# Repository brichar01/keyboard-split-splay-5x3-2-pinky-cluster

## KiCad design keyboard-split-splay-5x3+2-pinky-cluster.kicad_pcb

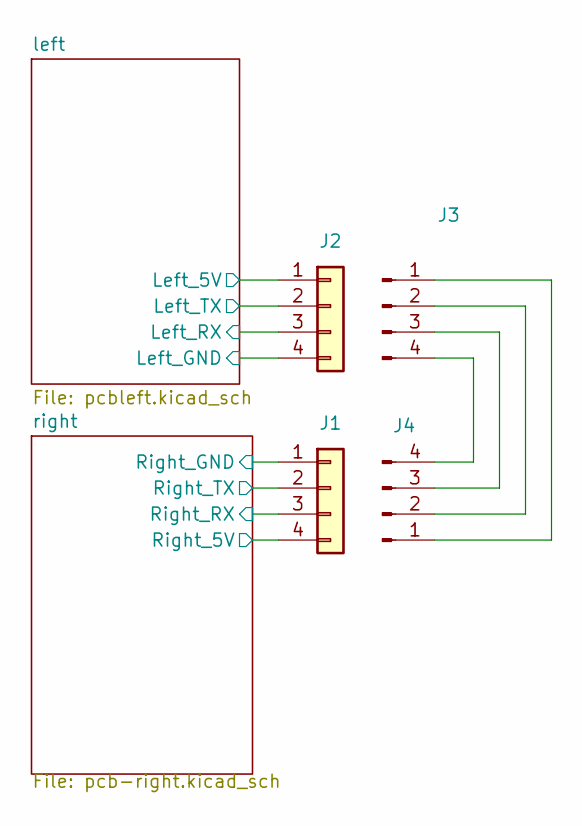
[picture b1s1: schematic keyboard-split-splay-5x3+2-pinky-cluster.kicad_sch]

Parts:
J1, J2: JST_SM04B-SR_R
J3, J4: Conn_01x04_Pin

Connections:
/left/LRX: J2.3; also elsewhere on the board
/left/LTX: J2.2; also elsewhere on the board
/left/L_5V: J2.1; also elsewhere on the board
/left/L_GND: J2.4; also elsewhere on the board
/right/RRX: J1.3; also elsewhere on the board
/right/RTX: J1.2; also elsewhere on the board
/right/R_5V: J1.4; also elsewhere on the board
/right/R_GND: J1.1; also elsewhere on the board
unnamed: J3.1, J4.1
unnamed: J3.2, J4.2
unnamed: J3.3, J4.3
unnamed: J3.4, J4.4

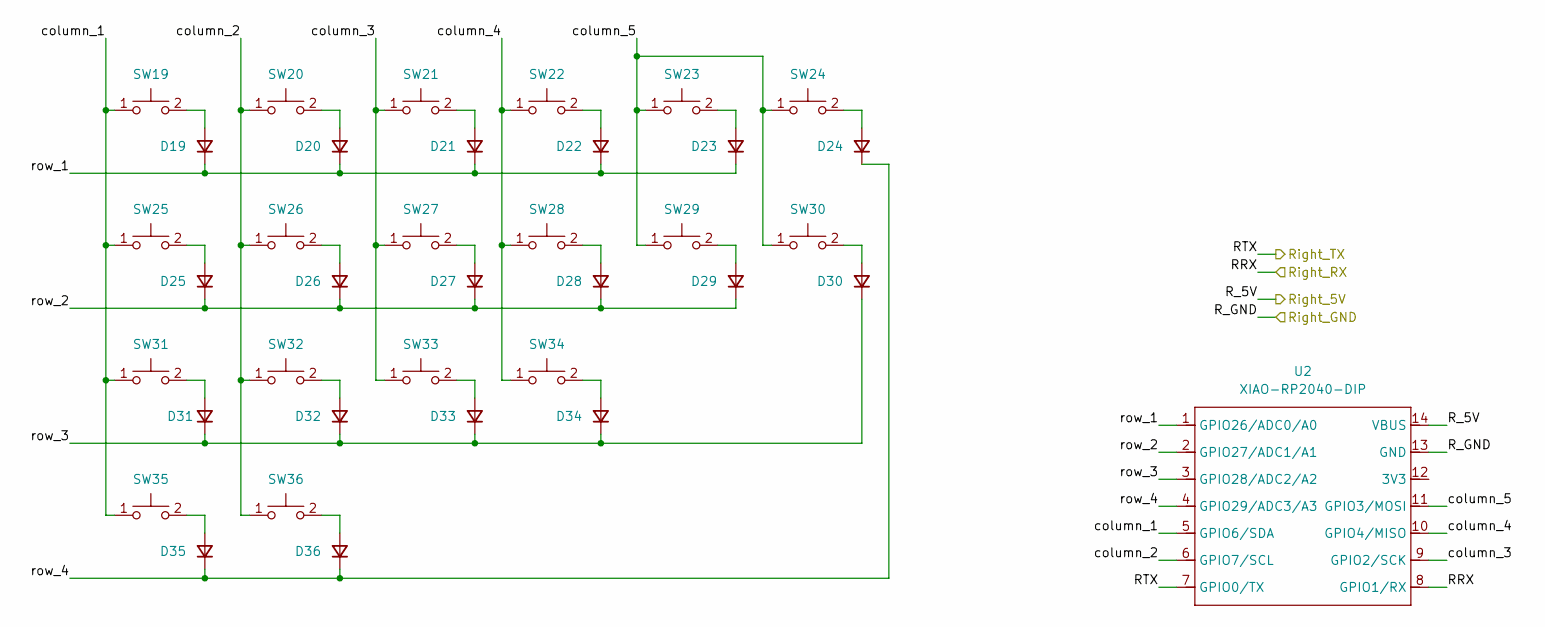
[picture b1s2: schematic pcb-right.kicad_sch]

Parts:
D19, D20, D21, D22, D23, D24, D25, D26, D27, D28, D29, D30, D31, D32, D33, D34, D35, D36: Val; GENERIC_DO-35_A
SW19, SW20, SW21, SW22, SW23, SW24, SW25, SW26, SW27, SW28, SW29, SW30, SW31, SW32, SW33, SW34, SW35, SW36: GENERIC_ELECTROMECHANICAL_PUSHBUTTON; GATEREON_KS-2P02B01-01-a_R
U2: XIAO-RP2040-DIP; SEEED_XIAO-RP2040_T-DIP

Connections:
/right/RRX: U2.8 (GPIO1/RX); also elsewhere on the board
/right/RTX: U2.7 (GPIO0/TX); also elsewhere on the board
/right/R_5V: U2.14 (VBUS); also elsewhere on the board
/right/R_GND: U2.13 (GND); also elsewhere on the board
/right/column_1: SW19.1 (2), SW25.1 (2), SW31.1 (2), SW35.1 (2), U2.5 (GPIO6/SDA)
/right/column_2: SW20.1 (2), SW26.1 (2), SW32.1 (2), SW36.1 (2), U2.6 (GPIO7/SCL)
/right/column_3: SW21.1 (2), SW27.1 (2), SW33.1 (2), U2.9 (GPIO2/SCK)
/right/column_4: SW22.1 (2), SW28.1 (2), SW34.1 (2), U2.10 (GPIO4/MISO)
/right/column_5: SW23.1 (2), SW24.1 (2), SW29.1 (2), SW30.1 (2), U2.11 (GPIO3/MOSI)
/right/row_1: D19.1 (K), D20.1 (K), D21.1 (K), D22.1 (K), D23.1 (K), U2.1 (GPIO26/ADC0/A0)
/right/row_2: D25.1 (K), D26.1 (K), D27.1 (K), D28.1 (K), D29.1 (K), U2.2 (GPIO27/ADC1/A1)
/right/row_3: D30.1 (K), D31.1 (K), D32.1 (K), D33.1 (K), D34.1 (K), U2.3 (GPIO28/ADC2/A2)
/right/row_4: D24.1 (K), D35.1 (K), D36.1 (K), U2.4 (GPIO29/ADC3/A3)
unnamed: D19.2 (A), SW19.2
unnamed: D20.2 (A), SW20.2
unnamed: D21.2 (A), SW21.2
unnamed: D22.2 (A), SW22.2
unnamed: D23.2 (A), SW23.2
unnamed: D24.2 (A), SW24.2
unnamed: D25.2 (A), SW25.2
unnamed: D26.2 (A), SW26.2
unnamed: D27.2 (A), SW27.2
unnamed: D28.2 (A), SW28.2
unnamed: D29.2 (A), SW29.2
unnamed: D30.2 (A), SW30.2
unnamed: D31.2 (A), SW31.2
unnamed: D32.2 (A), SW32.2
unnamed: D33.2 (A), SW33.2
unnamed: D34.2 (A), SW34.2
unnamed: D35.2 (A), SW35.2
unnamed: D36.2 (A), SW36.2

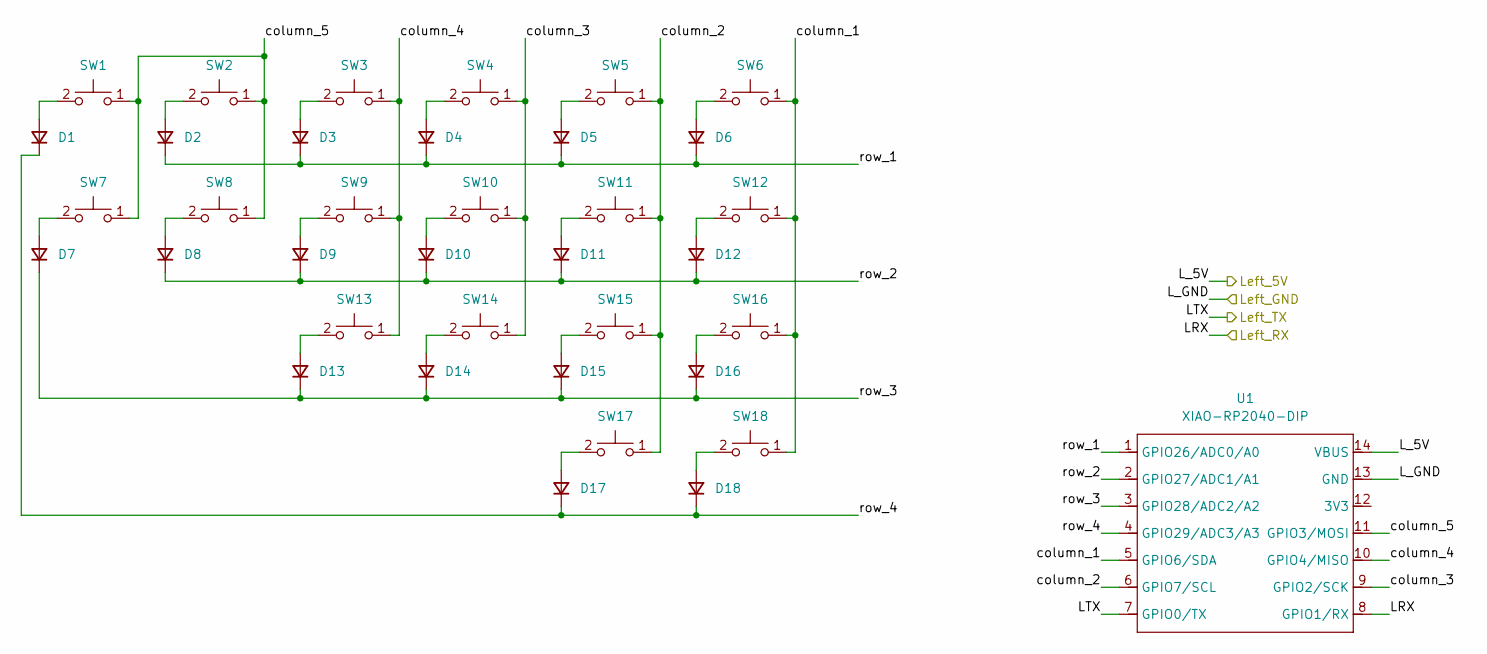
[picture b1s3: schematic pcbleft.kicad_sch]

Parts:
D1, D2, D3, D4, D5, D6, D7, D8, D9, D10, D11, D12, D13, D14, D15, D16, D17, D18: Val; GENERIC_DO-35_A
SW1, SW2, SW3, SW4, SW5, SW6, SW7, SW8, SW9, SW10, SW11, SW12, SW13, SW14, SW15, SW16, SW17, SW18: GENERIC_ELECTROMECHANICAL_PUSHBUTTON; GATEREON_KS-2P02B01-01-a_R
U1: XIAO-RP2040-DIP; SEEED_XIAO-RP2040_T-DIP

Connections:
/left/LRX: U1.8 (GPIO1/RX); also elsewhere on the board
/left/LTX: U1.7 (GPIO0/TX); also elsewhere on the board
/left/L_5V: U1.14 (VBUS); also elsewhere on the board
/left/L_GND: U1.13 (GND); also elsewhere on the board
/left/column_1: SW6.1 (2), SW12.1 (2), SW16.1 (2), SW18.1 (2), U1.5 (GPIO6/SDA)
/left/column_2: SW5.1 (2), SW11.1 (2), SW15.1 (2), SW17.1 (2), U1.6 (GPIO7/SCL)
/left/column_3: SW4.1 (2), SW10.1 (2), SW14.1 (2), U1.9 (GPIO2/SCK)
/left/column_4: SW3.1 (2), SW9.1 (2), SW13.1 (2), U1.10 (GPIO4/MISO)
/left/column_5: SW1.1 (2), SW2.1 (2), SW7.1 (2), SW8.1 (2), U1.11 (GPIO3/MOSI)
/left/row_1: D2.1 (K), D3.1 (K), D4.1 (K), D5.1 (K), D6.1 (K), U1.1 (GPIO26/ADC0/A0)
/left/row_2: D8.1 (K), D9.1 (K), D10.1 (K), D11.1 (K), D12.1 (K), U1.2 (GPIO27/ADC1/A1)
/left/row_3: D7.1 (K), D13.1 (K), D14.1 (K), D15.1 (K), D16.1 (K), U1.3 (GPIO28/ADC2/A2)
/left/row_4: D1.1 (K), D17.1 (K), D18.1 (K), U1.4 (GPIO29/ADC3/A3)
unnamed: D1.2 (A), SW1.2
unnamed: D2.2 (A), SW2.2
unnamed: D3.2 (A), SW3.2
unnamed: D4.2 (A), SW4.2
unnamed: D5.2 (A), SW5.2
unnamed: D6.2 (A), SW6.2
unnamed: D7.2 (A), SW7.2
unnamed: D8.2 (A), SW8.2
unnamed: D9.2 (A), SW9.2
unnamed: D10.2 (A), SW10.2
unnamed: D11.2 (A), SW11.2
unnamed: D12.2 (A), SW12.2
unnamed: D13.2 (A), SW13.2
unnamed: D14.2 (A), SW14.2
unnamed: D15.2 (A), SW15.2
unnamed: D16.2 (A), SW16.2
unnamed: D17.2 (A), SW17.2
unnamed: D18.2 (A), SW18.2

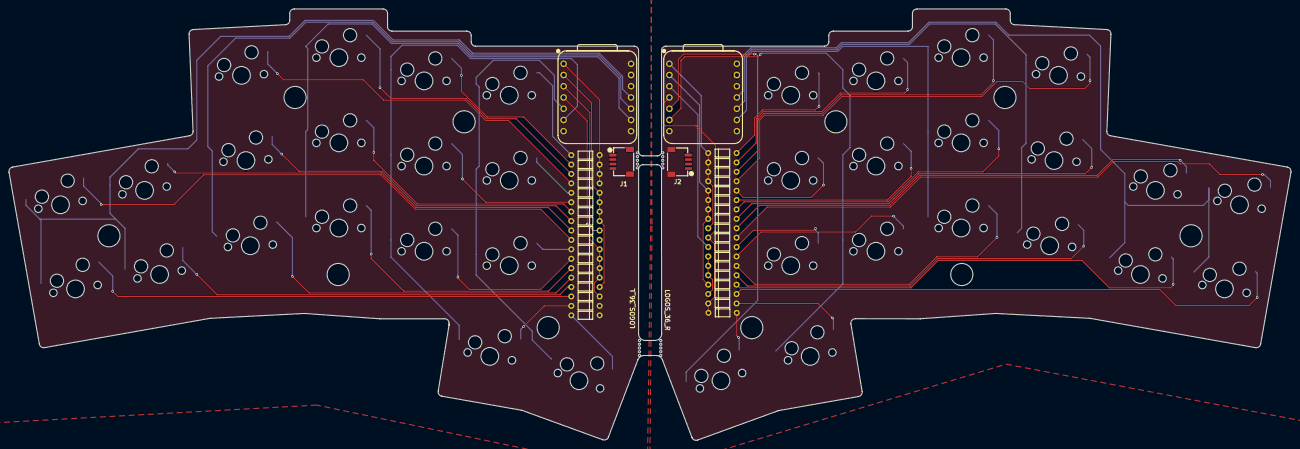
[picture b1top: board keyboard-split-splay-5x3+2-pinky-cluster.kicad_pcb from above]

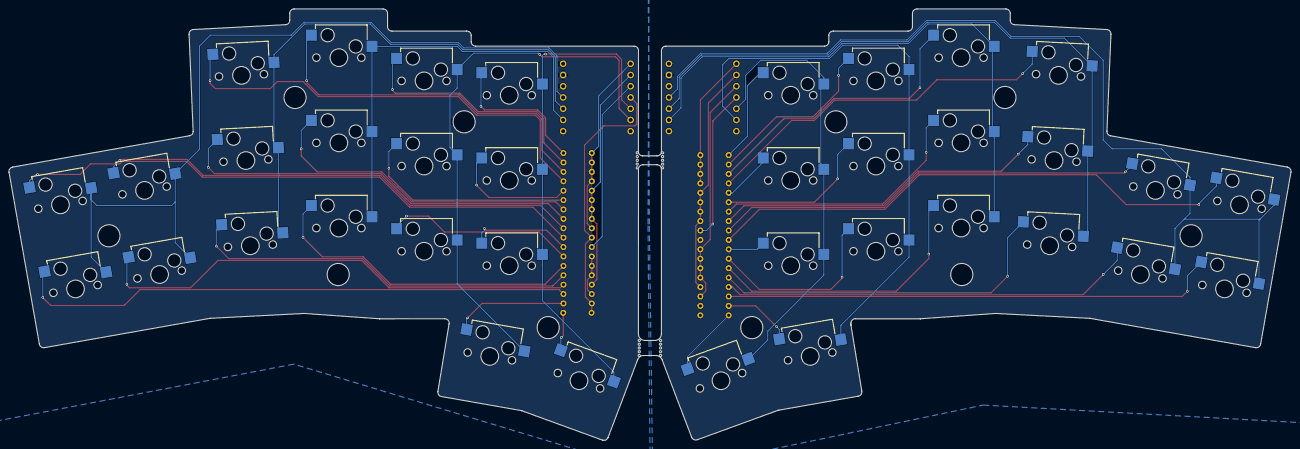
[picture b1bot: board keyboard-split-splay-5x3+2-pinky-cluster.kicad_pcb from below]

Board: 2 copper layers, 289.7 x 97.5 mm, 77 parts (36 on the bottom side), 62 nets.

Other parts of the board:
M2: MECHANICAL_HOLE_5MM

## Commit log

2026-01-03 Initial release
2026-01-03 Gitignore
2026-01-03 Remove ignored files
2026-01-11 Rev 1.1, fix diode footprints, add plate and base generation jobs, add mouse bites and some extra solder jumpers
2026-01-11 Touchups and name: Logos
2026-02-09 Base and plate, updates to library, fix diode footprint and symmetry
2026-04-03 Latest release
2026-04-05 Through hole layout
